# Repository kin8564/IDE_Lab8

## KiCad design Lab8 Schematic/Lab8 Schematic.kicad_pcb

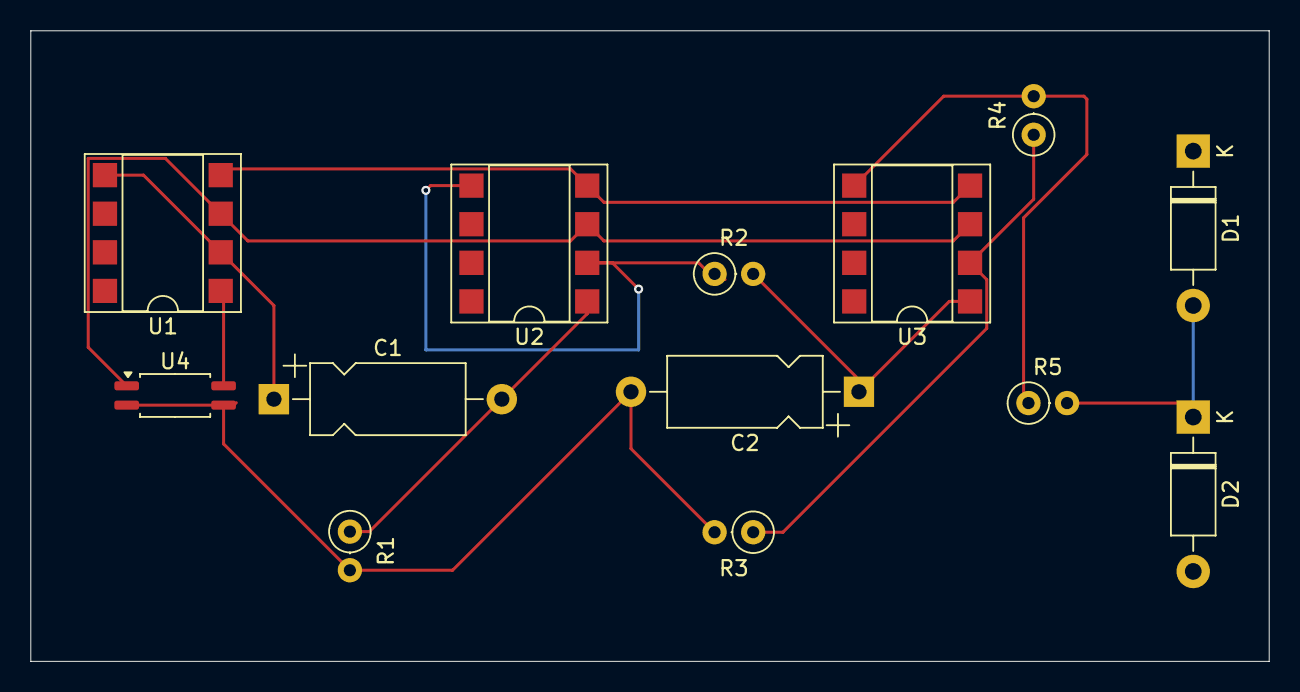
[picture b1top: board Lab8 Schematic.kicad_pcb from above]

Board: 2 copper layers, 81.5 x 41.5 mm, 13 parts (0 on the bottom side), 11 nets.

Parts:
C1: 19u; CP_Axial_L10.0mm_D4.5mm_P15.00mm_Horizontal
C2: 4u; CP_Axial_L10.0mm_D4.5mm_P15.00mm_Horizontal
D1, D2: 1N5819; D_DO-41_SOD81_P10.16mm_Horizontal
R1, R2: 10k; R_Axial_DIN0207_L6.3mm_D2.5mm_P2.54mm_Vertical
R3: 1k; R_Axial_DIN0207_L6.3mm_D2.5mm_P2.54mm_Vertical
R4: 28k; R_Axial_DIN0207_L6.3mm_D2.5mm_P2.54mm_Vertical
R5: 100; R_Axial_DIN0207_L6.3mm_D2.5mm_P2.54mm_Vertical
U1, U2, U3: DIP-8_W7.62mm_SMDSocket_SmallPads
U4: ACPL-214-500E; SOP-4_4.4x2.6mm_P1.27mm

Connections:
+5V: U1.3 (V+), U2.3 (V+), U3.3 (V+), U4.1
-5V: U1.4 (V-), U2.4 (V-), U3.4 (V-)
GND: C2.2, R1.2, R3.2, U4.2, U4.3
unnamed: D1.2 (A), D2.1 (K), R5.2
unnamed: R4.2, R5.1, U3.5
unnamed: U1.1 (+), U4.4
unnamed: C1.1, U1.2 (-), U1.5
unnamed: C1.2, R1.1, U2.1 (+)
unnamed: R2.1, U2.2 (-), U2.5
unnamed: C2.1, R2.2, U3.1 (+)
unnamed: R3.1, R4.1, U3.2 (-)

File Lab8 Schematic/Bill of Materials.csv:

"Reference","Value","Datasheet","Footprint","Qty","DNP"
"C1","19u","~","Capacitor_THT:CP_Axial_L10.0mm_D4.5mm_P15.00mm_Horizontal","1",""
"C2","4u","~","Capacitor_THT:CP_Axial_L10.0mm_D4.5mm_P15.00mm_Horizontal","1",""
"D1,D2","1N5819","http://www.vishay.com/docs/88525/1n5817.pdf","Diode_THT:D_DO-41_SOD81_P10.16mm_Horizontal","2",""
"R1,R2","10k","~","Resistor_THT:R_Axial_DIN0207_L6.3mm_D2.5mm_P2.54mm_Vertical","2",""
"R3","1k","~","Resistor_THT:R_Axial_DIN0207_L6.3mm_D2.5mm_P2.54mm_Vertical","1",""
"R4","28k","~","Resistor_THT:R_Axial_DIN0207_L6.3mm_D2.5mm_P2.54mm_Vertical","1",""
"R5","100","~","Resistor_THT:R_Axial_DIN0207_L6.3mm_D2.5mm_P2.54mm_Vertical","1",""
"U1,U2,U3","","https://ngspice.sourceforge.io/docs/ngspice-html-manual/manu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","Package_DIP:DIP-8_W7.62mm_SMDSocket_SmallPads","3",""
"U4","ACPL-214-500E","https://docs.broadcom.com/doc/AV02-0469EN","Package_SO:SOP-4_4.4x2.6mm_P1.27mm","1",""

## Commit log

2024-10-30 Initialized repo. ADC code copied from Lab5
2024-11-04 Update Lab8-ADC.c
    Added logic to time pulses and calculate BPM, don't know what the threshold should be
2024-11-06 LTspice signed off last week
2024-11-08 Fleshed out ADC code, need to finish calculations
2024-11-08 ADC Code signed off
2024-11-11 Added kiCad schematics
2024-11-12 KiCad schematic done, PCB has a strange error
2024-11-12 All signoffs received
